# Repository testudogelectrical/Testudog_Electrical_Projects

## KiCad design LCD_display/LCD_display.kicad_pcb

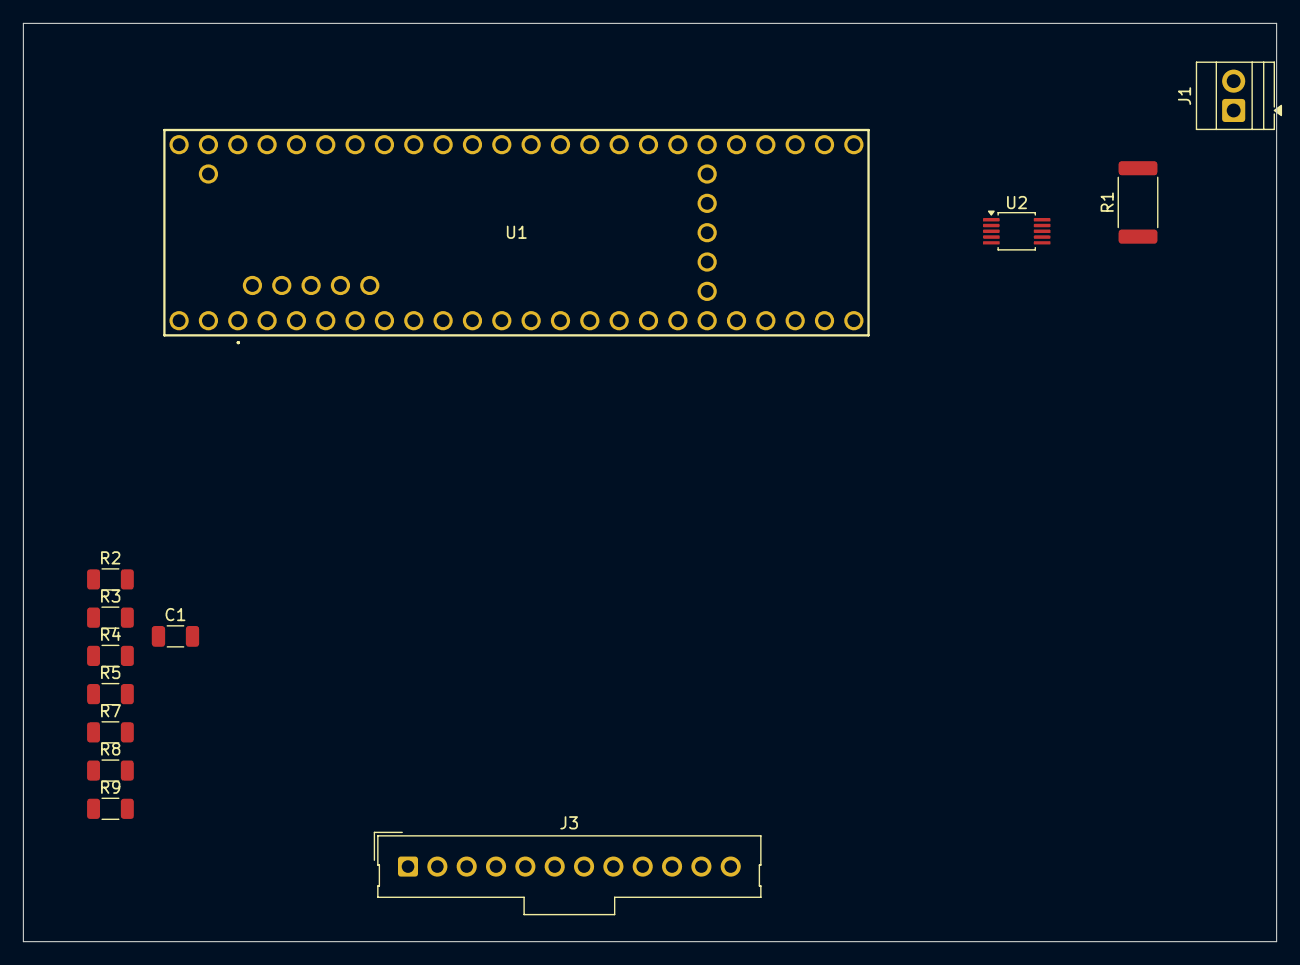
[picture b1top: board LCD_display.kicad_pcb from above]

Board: 2 copper layers, 108.5 x 79.5 mm, 13 parts (0 on the bottom side), 23 nets, no tracks yet.

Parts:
C1: C_Small; C_1206_3216Metric
J1: Screw_Terminal_01x02; TerminalBlock_Xinya_XY308-2.54-2P_1x02_P2.54mm_Horizontal
J3: Conn_01x12_Pin; Molex_SL_171971-0012_1x12_P2.54mm_Vertical
R1: R_Shunt_US; R_2512_6332Metric
R2, R3, R4, R5, R7, R8, R9: 220; R_1206_3216Metric
U1: Teensy4.1; TEENSY41
U2: INA226; VSSOP-10_3x3mm_P0.5mm

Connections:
3V3: C1.1, J3.10, U1.46 (3V3), U2.6 (VS)
+V_SUPPLY_BUS: J1.2, R1.1, U2.8 (Vbus)
Button_in: J3.11, U1.32 (40_A16)
GND: C1.2, J3.12, U1.1 (GND), U2.1 (A1), U2.2 (A0), U2.7 (GND)
LED1: J3.8, U1.13 (11_MOSI_CTX1)
LED2: J3.9, U1.14 (12_MISO_MQSL)
unnamed: R2.1, U1.5 (3_LRCLK2)
unnamed: R3.1, U1.6 (4_BCLK2)
unnamed: R4.1, U1.7 (5_IN2)
unnamed: R5.1, U1.8 (6_OUT1D)
unnamed: R7.1, U1.9 (7_RX2_OUT1A)
unnamed: R8.1, U1.10 (8_TX2_IN1)
unnamed: R9.1, U1.11 (9_OUT1C)
unnamed: R1.2, U2.10 (Vin+)
SCL_4.1: U1.41 (19_A5_SCL), U2.5 (SCL)
SDA_4.1: U1.40 (18_A4_SDA), U2.4 (SDA)
SEG_A: J3.1, R2.2
SEG_B: J3.2, R3.2
SEG_C: J3.3, R4.2
SEG_D: J3.4, R5.2
SEG_E: J3.5, R7.2
SEG_F: J3.6, R8.2
SEG_G: J3.7, R9.2
